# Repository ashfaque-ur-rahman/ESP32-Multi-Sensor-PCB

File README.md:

# ESP32-C3 Multi-Sensor PCB — 4-Layer Board
 
My most complex PCB design to date — an ESP32-C3 based multi-sensor IoT board featuring three sensors across a hierarchical, multi-sheet schematic. Designed over multiple days following the **Tech Explorations** tutorial series. This was my first experience with both 4-layer PCB stackup design and microphone amplifier circuit design.
 
---
 
## Preview
 
### Schematic — Root Page

### Schematic — Sensors Sheet

### Schematic — Page 2

### Schematic — User Interface Sheet

### PCB Layout

### 3D View

---
 
## Project overview
 
| Property | Details |
|---|---|
| **MCU** | ESP32-C3 |
| **Board layers** | 4-layer stackup |
| **Schematic structure** | Hierarchical — 3 separate sheets |
| **Sensors** | BME280, Electret Microphone + MAX4466EXK |
| **EDA Tool** | KiCad 9.0 |
| **Design reference** | Tech Explorations tutorial series |
| **Status** | Design complete |
 
---
 
## Board stackup
 
| Layer | Function |
|---|---|
| Layer 1 (Top) | Signal + components |
| Layer 2 | Ground plane (GND) |
| Layer 3 | Power plane (VCC) |
| Layer 4 (Bottom) | Signal |
 
A dedicated ground plane on Layer 2 ensures low-impedance returns for all sensors and clean power distribution — critical for analog microphone signal integrity.
 
---
 
## Sensors & key components
 
| Component | Part | Function | Interface |
|---|---|---|---|
| Environmental Sensor | BME280 (Bosch) | Temperature, humidity & pressure — 3-in-1 | I²C / SPI |
| Microphone | CMC-5042PF-AC (Same Sky) | 6mm omnidirectional electret condenser mic | Analog |
| Mic Amplifier | MAX4466EXK (Analog Devices) | Low-noise microphone amplifier, SC-70 package | Analog |
| MCU | ESP32-C3-02 | Wi-Fi + Bluetooth 5.0 LE microcontroller | — |
 
---
 
## Schematic structure
 
This design uses a **hierarchical multi-sheet schematic** — a professional approach for managing complex designs:
 
| Sheet | Contents |
|---|---|
| `Root page 1` | Top-level hierarchy, power distribution, ESP32-C3 core |
| `sensors.kicad_sch` | BME280 environmental sensor + microphone + MAX4466 amplifier circuit |
| `user_interface.kicad_sch` | User-facing connections, GPIO breakouts, connectors |
 
---
 
## Files included
 
### KiCad project files
| File | Description |
|---|---|
| `1st_ESP32_Demo_project.kicad_pro` | KiCad project file |
| `1st_ESP32_Demo_project.kicad_sch` | Root schematic |
| `ESP32-C3-02.kicad_sch` | ESP32-C3 sub-schematic sheet |
| `sensors.kicad_sch` | Sensors sub-schematic sheet |
| `user_interface.kicad_sch` | User interface sub-schematic sheet |
| `1st_ESP32_Demo_project.kicad_pcb` | PCB layout |
| `Footprints/` | Custom footprint library |
 
---
 
## What I learned
 
- 4-layer PCB stackup design with dedicated ground and power planes
- Hierarchical multi-sheet schematic design in KiCad 9.0
- BME280 I²C sensor integration with proper decoupling
- Electret condenser microphone biasing and signal conditioning
- MAX4466EXK low-noise amplifier circuit design
- Analog signal routing considerations on a mixed-signal PCB
- ESP32-C3 peripheral assignment and RF antenna clearance
---
 
## Tools used

---
 
## Reference
 
This design follows the **Tech Explorations ESP32 PCB Design tutorial series**.
 
> Tech Explorations: [https://www.youtube.com/@TechExplorations](https://www.youtube.com/@TechExplorations)
 
---
 
*Mymensingh Engineering College — EEE Department*

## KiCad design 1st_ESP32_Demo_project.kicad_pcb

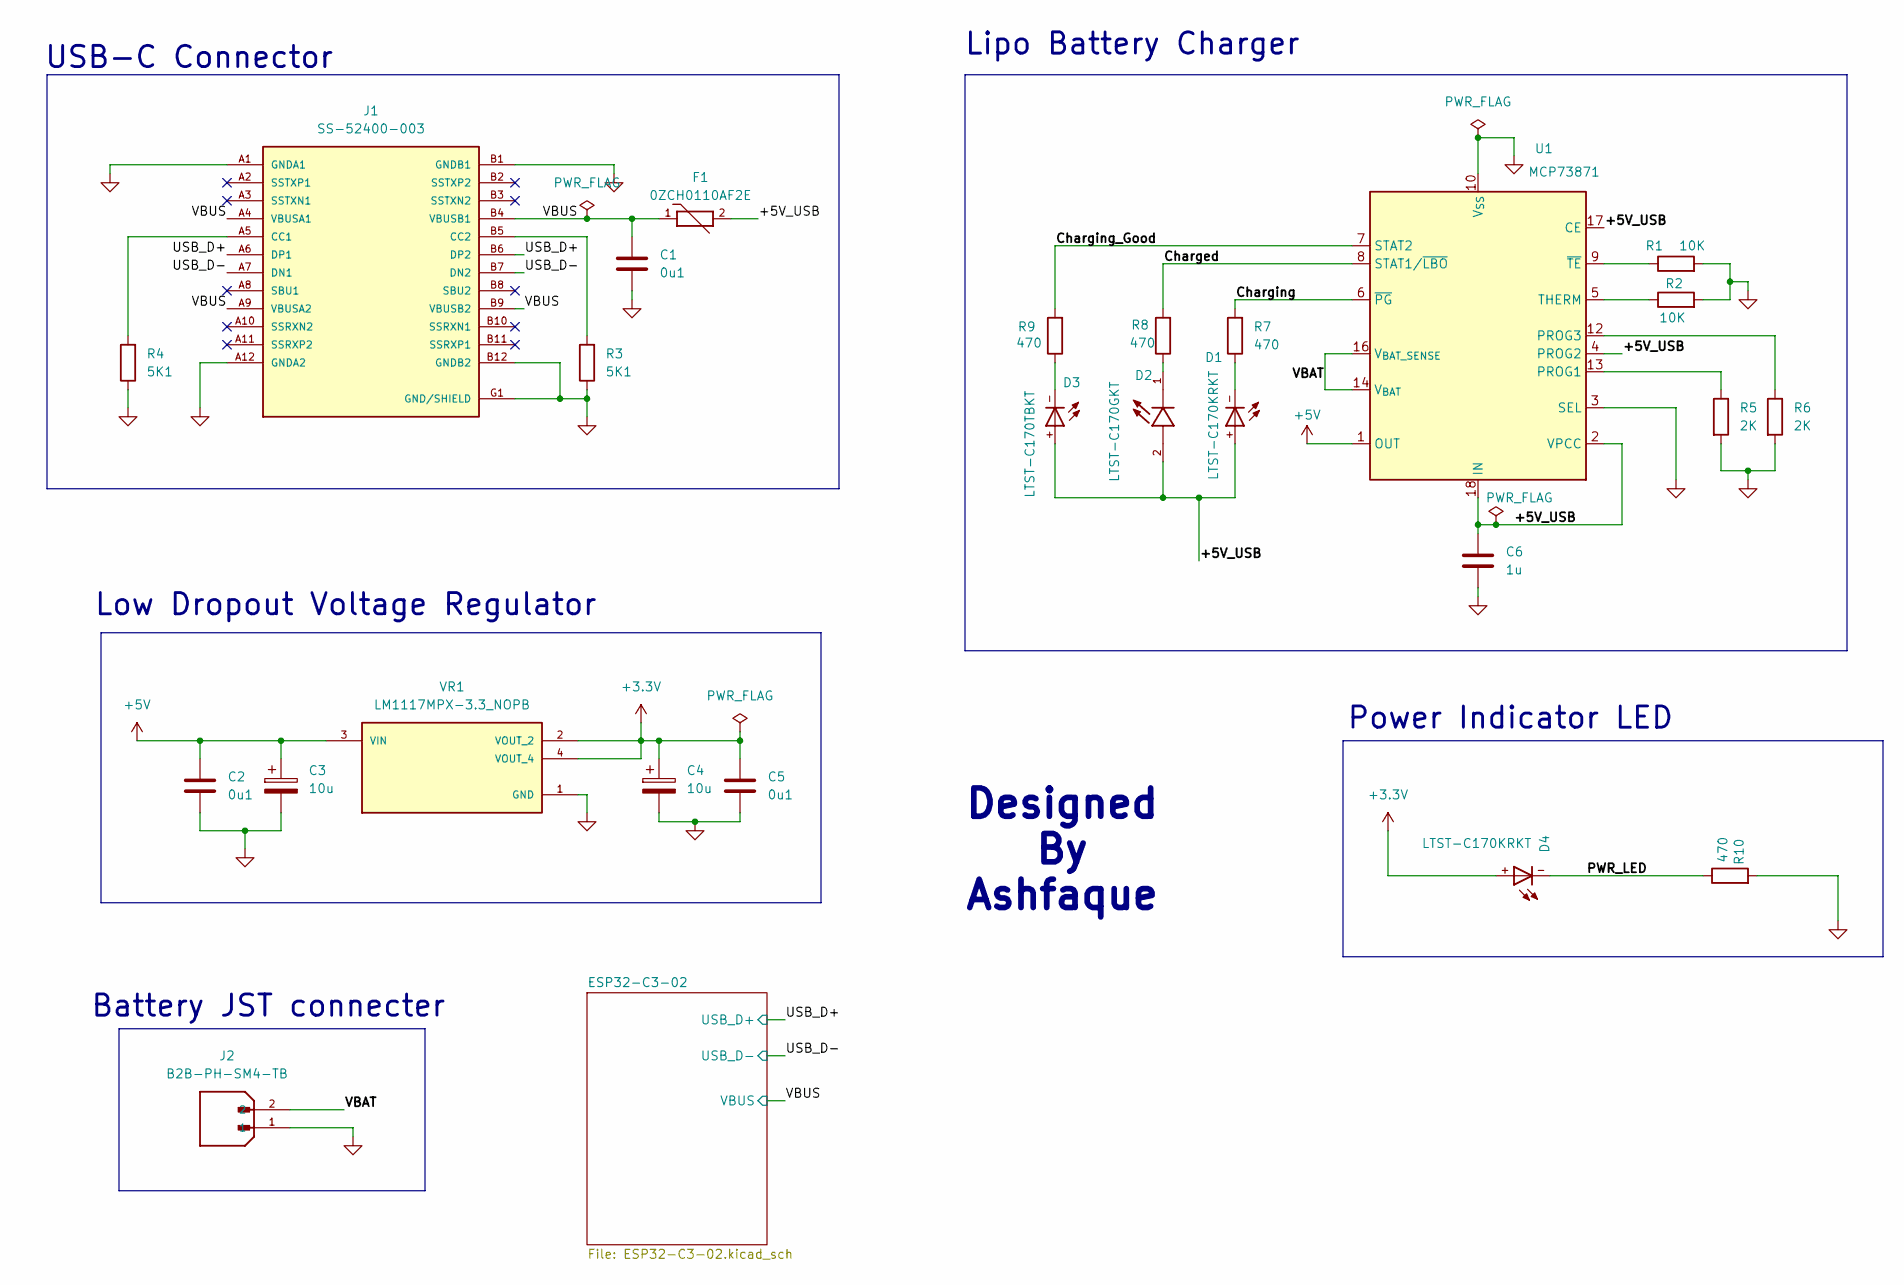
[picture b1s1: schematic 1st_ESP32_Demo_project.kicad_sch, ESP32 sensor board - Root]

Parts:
C1, C2, C5: 0u1; C_0805_2012Metric
C3, C4: 10u; CP_EIA-2012-12_Kemet-R
C6: 1u; C_0805_2012Metric
D1, D4: LTST-C170KRKT; DIOC200X125X110
D2: LTST-C170GKT; LED_LTST-C170GKT; PARTREV I
D3: LTST-C170TBKT; DIOC200X125X110
F1: 0ZCH0110AF2E; FUSC3225X100N; PARTREV Apr2023
J1: SS-52400-003; BELFUSE_SS-52400-003; PARTREV A0
J2: B2B-PH-SM4-TB; JST_B2B-PH-SM4-TB; PARTREV N/A
R1, R2: 10K; R_0805_2012Metric
R3, R4: 5K1; R_0805_2012Metric
R5, R6: 2K; R_0805_2012Metric
R7, R8, R9, R10: 470; R_0805_2012Metric
U1: MCP73871; QFN-20-1EP_4x4mm_P0.5mm_EP2.5x2.5mm
VR1: LM1117MPX-3.3_NOPB; VREG_LM1117MPX-3.3_NOPB; PARTREV O

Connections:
+3.3V: C4.1, C5.1, D4.+, VR1.2 (VOUT_2), VR1.4 (VOUT_4); also elsewhere on the board
+5V: C2.1, C3.1, U1.1 (OUT), U1.20 (OUT), VR1.3 (VIN)
/+5V_USB: C6.1, D1.+, D2.2, D3.+, F1.2, U1.2 (VPCC), U1.4 (PROG2), U1.17 (CE), U1.18 (IN), U1.19 (IN); also elsewhere on the board
/Charged: R8.2, U1.8 (STAT1/~LBO)
/Charging: R7.2, U1.6 (~PG)
/Charging_Good: R9.2, U1.7 (STAT2)
/PWR_LED: D4.-, R10.1
/USB_D+: J1.A6 (DP1), J1.B6 (DP2); also elsewhere on the board
/USB_D-: J1.A7 (DN1), J1.B7 (DN2); also elsewhere on the board
/VBAT: J2.2, U1.14 (V_{BAT}), U1.15 (V_{BAT}), U1.16 (V_{BAT_SENSE})
/VBUS: C1.1, F1.1, J1.A4 (VBUSA1), J1.A9 (VBUSA2), J1.B4 (VBUSB1), J1.B9 (VBUSB2); also elsewhere on the board
GND: C1.2, C2.2, C3.2, C4.2, C5.2, C6.2, J1.A1 (GNDA1), J1.A12 (GNDA2), J1.B1 (GNDB1), J1.B12 (GNDB2), J1.G1 (GND/SHIELD), J1.G2 (GND/SHIELD), J1.G3 (GND/SHIELD), J1.G4 (GND/SHIELD), J1.S1 (GND/SHIELD), J1.S2 (GND/SHIELD), J1.S3 (GND/SHIELD), J1.S4 (GND/SHIELD), J2.1, R1.2, R2.2, R3.1, R4.1, R5.2, R6.2, R10.2, U1.3 (SEL), U1.10 (V_{SS}), U1.11 (V_{SS}), U1.21 (V_{SS}), VR1.1 (GND); also elsewhere on the board
unnamed 35: D1.-, R7.1; also elsewhere on the board
unnamed 36: D2.1, R8.1; also elsewhere on the board
unnamed: D3.-, R9.1
unnamed: J1.A5 (CC1), R4.2
unnamed: J1.B5 (CC2), R3.2
unnamed: R5.1, U1.13 (PROG1)
unnamed: R6.1, U1.12 (PROG3)
unnamed: R2.1, U1.5 (THERM)
unnamed: R1.1, U1.9 (~TE)

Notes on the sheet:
Lipo Battery Charger
USB-C Connector
Battery JST connecter
Designed By Ashfaque
Power Indicator LED
Low Dropout Voltage Regulator

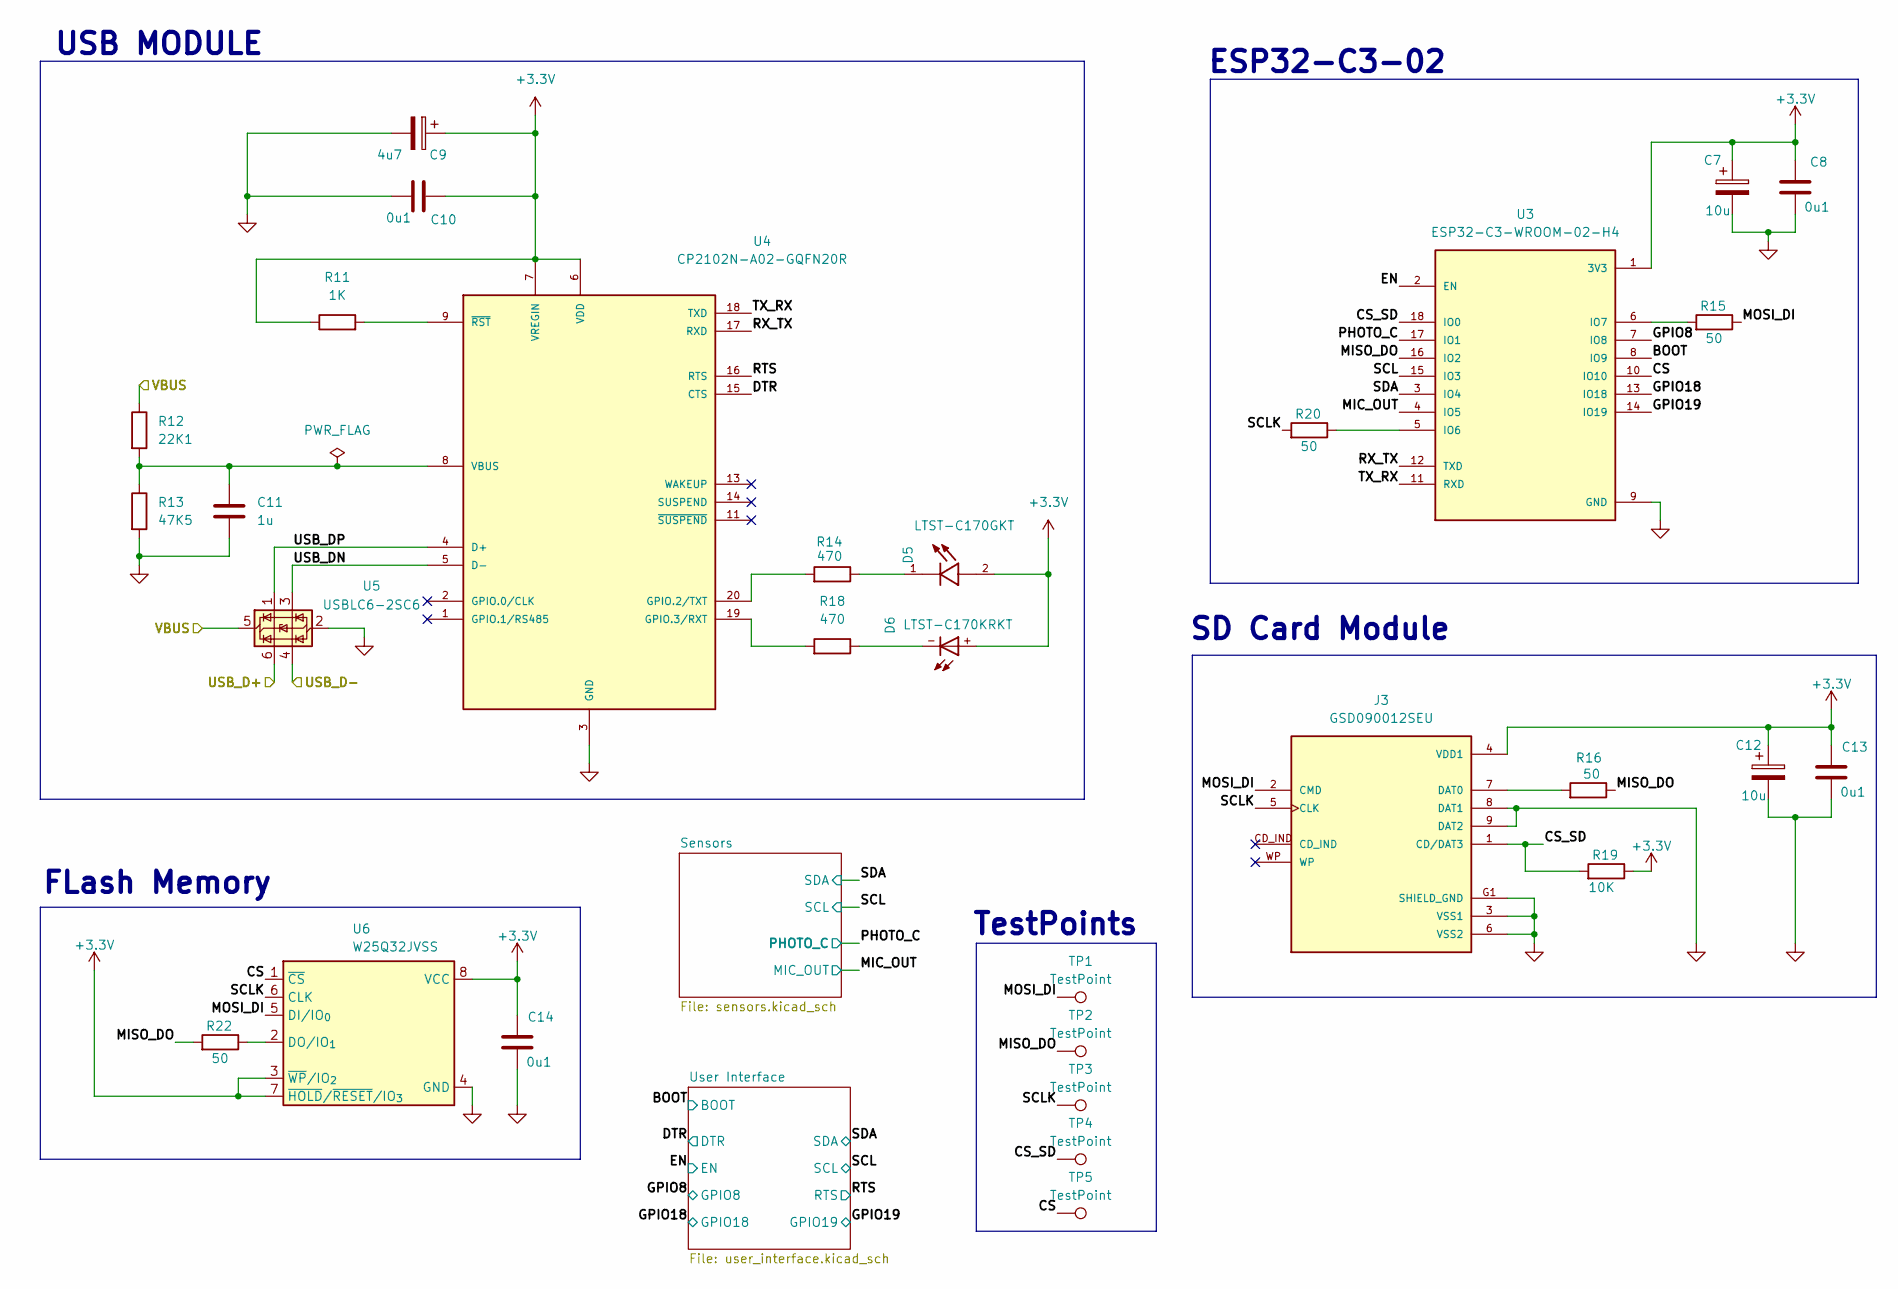
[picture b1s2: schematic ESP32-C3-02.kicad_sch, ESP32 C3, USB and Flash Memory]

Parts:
C7, C12: 10u; CP_EIA-2012-12_Kemet-R
C8, C10, C13, C14: 0u1; C_0805_2012Metric
C9: 4u7; CP_EIA-2012-12_Kemet-R
C11: 1u; C_0805_2012Metric
D5: LTST-C170GKT; LED_LTST-C170GKT; PARTREV I
D6: LTST-C170KRKT; DIOC200X125X110
J3: GSD090012SEU; AMPHENOL_GSD090012SEU; PARTREV E
R11: 1K; R_0805_2012Metric
R12: 22K1; R_0805_2012Metric
R13: 47K5; R_0805_2012Metric
R14, R18: 470; R_0805_2012Metric
R15, R16, R20, R22: 50; R_0805_2012Metric
R19: 10K; R_0805_2012Metric
TP1, TP2, TP3, TP4, TP5: TestPoint; TestPoint_Pad_D1.0mm
U3: ESP32-C3-WROOM-02-H4; MODULE_ESP32-C3-WROOM-02-H4
U4: CP2102N-A02-GQFN20R; SiliconLabs_QFN-20-1EP_3x3mm_P0.5mm_EP1.8x1.8mm; PARTREV 1.3
U5: USBLC6-2SC6; SOT-23-6
U6: W25Q32JVSS; SOIC-8_5.3x5.3mm_P1.27mm

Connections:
+3.3V: C7.1, C8.2, C9.1, C10.2, C12.1, C13.2, C14.2, D5.2, D6.+, J3.4 (VDD1), R11.1, R19.1, U3.1 (3V3), U4.6 (VDD), U4.7 (VREGIN), U6.3 (~WP/IO_{2}), U6.7 (~HOLD/~RESET/IO_{3}), U6.8 (VCC); also elsewhere on the board
/ESP32-C3-02/BOOT: U3.8 (IO9); also elsewhere on the board
/ESP32-C3-02/CS: TP5.1, U3.10 (IO10), U6.1 (~CS); also elsewhere on the board
/ESP32-C3-02/CS_SD: J3.1 (CD/DAT3), R19.2, TP4.1, U3.18 (IO0); also elsewhere on the board
/ESP32-C3-02/DTR: U4.15 (CTS); also elsewhere on the board
/ESP32-C3-02/EN: U3.2 (EN); also elsewhere on the board
/ESP32-C3-02/GPIO8: U3.7 (IO8); also elsewhere on the board
/ESP32-C3-02/GPIO18: U3.13 (IO18); also elsewhere on the board
/ESP32-C3-02/GPIO19: U3.14 (IO19); also elsewhere on the board
/ESP32-C3-02/MIC_OUT: U3.4 (IO5); also elsewhere on the board
/ESP32-C3-02/MISO_DO: R16.1, R22.2, TP2.1, U3.16 (IO2); also elsewhere on the board
/ESP32-C3-02/MOSI_DI: J3.2 (CMD), R15.1, TP1.1, U6.5 (DI/IO_{0}); also elsewhere on the board
/ESP32-C3-02/PHOTO_C: U3.17 (IO1); also elsewhere on the board
/ESP32-C3-02/RTS: U4.16 (RTS); also elsewhere on the board
/ESP32-C3-02/RX_TX: U3.12 (TXD), U4.17 (RXD)
/ESP32-C3-02/SCL: U3.15 (IO3); also elsewhere on the board
/ESP32-C3-02/SCLK: J3.5 (CLK), R20.2, TP3.1, U6.6 (CLK); also elsewhere on the board
/ESP32-C3-02/SDA: U3.3 (IO4); also elsewhere on the board
/ESP32-C3-02/TX_RX: U3.11 (RXD), U4.18 (TXD)
/ESP32-C3-02/USB_DN: U4.5 (D-), U5.3 (I/O2)
/ESP32-C3-02/USB_DP: U4.4 (D+), U5.1 (I/O1)
/USB_D+: U5.6 (I/O1); also elsewhere on the board
/USB_D-: U5.4 (I/O2); also elsewhere on the board
/VBUS: R12.1, U5.5 (VBUS); also elsewhere on the board
GND: C7.2, C8.1, C9.2, C10.1, C11.2, C12.2, C13.1, C14.1, J3.3 (VSS1), J3.6 (VSS2), J3.8 (DAT1), J3.9 (DAT2), J3.G1 (SHIELD_GND), J3.G2 (SHIELD_GND), J3.G3 (SHIELD_GND), J3.G4 (SHIELD_GND), R13.2, U3.9 (GND), U3.19 (GND), U3.20 (GND), U3.21 (GND), U3.22 (GND), U3.23 (GND), U3.24 (GND), U3.25 (GND), U3.26 (GND), U3.27 (GND), U3.28 (GND), U3.29 (GND), U3.30 (GND), U3.31 (GND), U3.32 (GND), U3.33 (GND), U3.34 (GND), U3.35 (GND), U3.36 (GND), U3.37 (GND), U3.38 (GND), U3.39 (GND), U4.3 (GND), U4.12 (GND), U4.21 (GND), U5.2 (GND), U6.4 (GND); also elsewhere on the board
unnamed: D5.1, R14.1
unnamed: D6.-, R18.1
unnamed: J3.7 (DAT0), R16.2
unnamed: R20.1, U3.5 (IO6)
unnamed: R15.2, U3.6 (IO7)
unnamed: R14.2, U4.20 (GPIO.2/TXT)
unnamed: R18.2, U4.19 (GPIO.3/RXT)
unnamed: C11.1, R12.2, R13.1, U4.8 (VBUS)
unnamed: R11.2, U4.9 (~RST)
unnamed: R22.1, U6.2 (DO/IO_{1})

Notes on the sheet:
USB MODULE
FLash Memory
ESP32-C3-02
TestPoints
SD Card Module

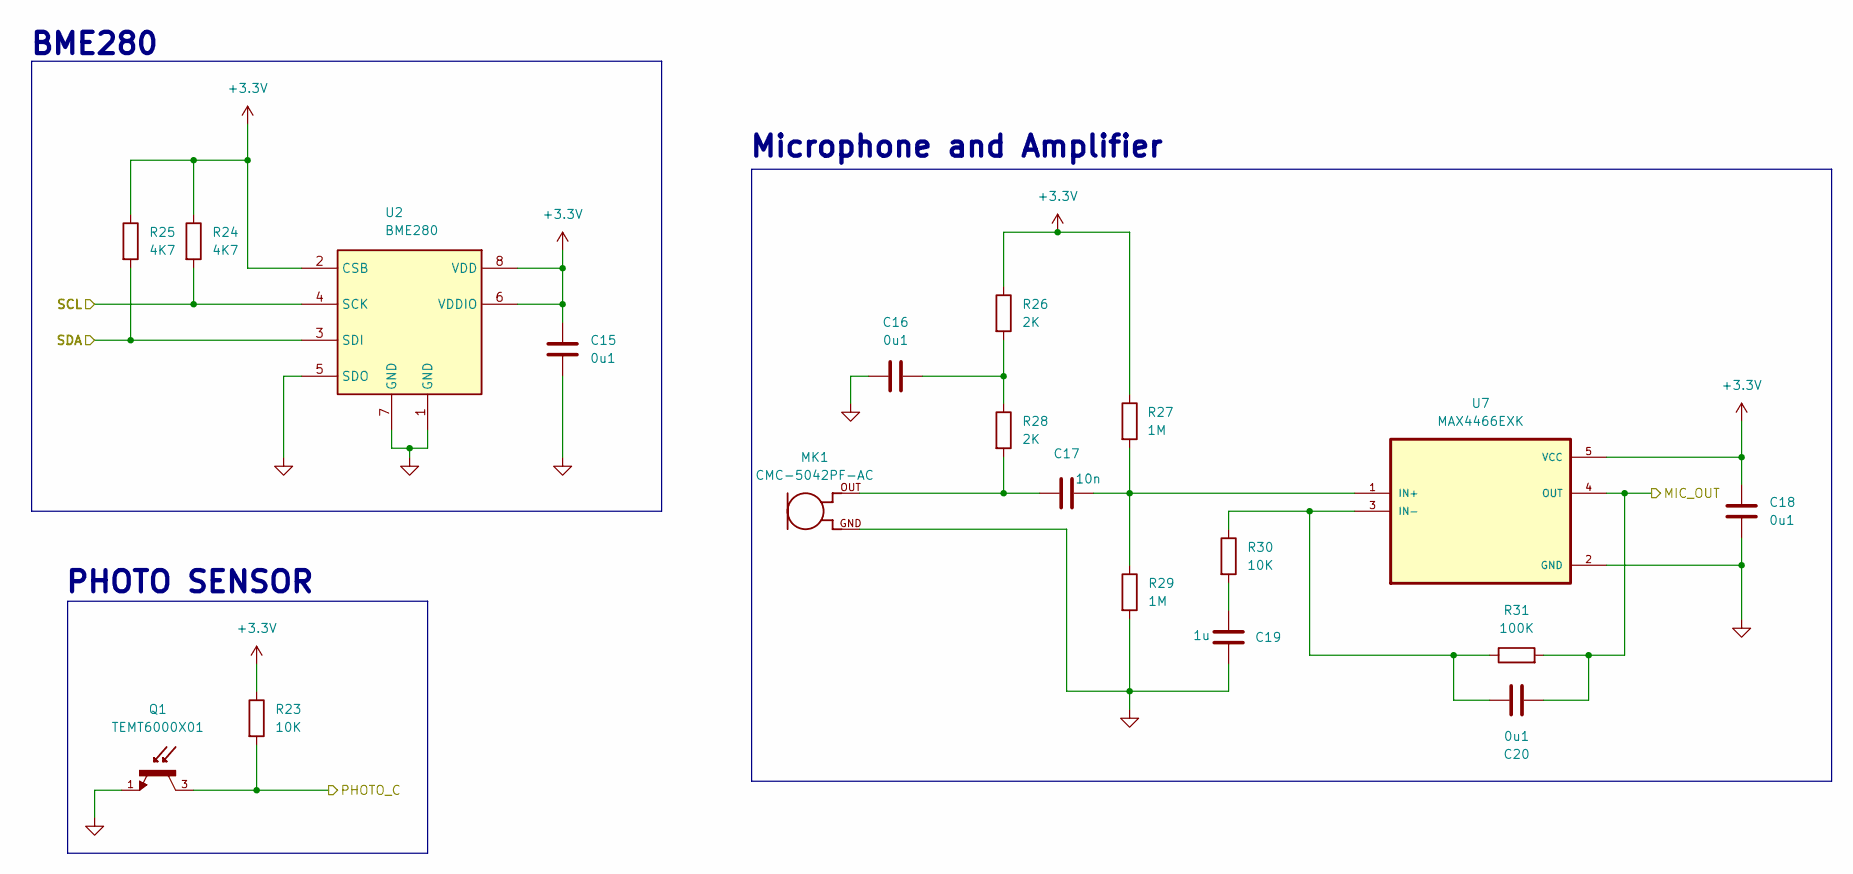
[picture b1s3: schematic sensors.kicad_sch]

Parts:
C15, C16, C18, C20: 0u1; C_0805_2012Metric
C17: 10n; C_0805_2012Metric
C19: 1u; C_0805_2012Metric
MK1: CMC-5042PF-AC; CUI_CMC-5042PF-AC
Q1: TEMT6000X01; TRANS_TEMT6000X01; PARTREV 1.9
R23, R30: 10K; R_0805_2012Metric
R24, R25: 4K7; R_0805_2012Metric
R26, R28: 2K; R_0805_2012Metric
R27, R29: 1M; R_0805_2012Metric
R31: 100K; R_0805_2012Metric
U2: BME280; Bosch_LGA-8_2.5x2.5mm_P0.65mm_ClockwisePinNumbering
U7: MAX4466EXK; SOT65P210X110-5N

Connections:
+3.3V: C15.1, C18.1, R23.1, R24.1, R25.1, R26.1, R27.1, U2.2 (CSB), U2.6 (VDDIO), U2.8 (VDD), U7.5 (VCC); also elsewhere on the board
/ESP32-C3-02/MIC_OUT: C20.2, R31.2, U7.4 (OUT); also elsewhere on the board
/ESP32-C3-02/PHOTO_C: Q1.3, R23.2; also elsewhere on the board
/ESP32-C3-02/SCL: R24.2, U2.4 (SCK); also elsewhere on the board
/ESP32-C3-02/SDA: R25.2, U2.3 (SDI); also elsewhere on the board
GND: C15.2, C16.1, C18.2, C19.1, MK1.GND, Q1.1, R29.2, U2.1 (GND), U2.5 (SDO), U2.7 (GND), U7.2 (GND); also elsewhere on the board
unnamed: C16.2, R26.2, R28.1
unnamed: C17.2, MK1.OUT, R28.2
unnamed: C19.2, R30.2
unnamed: C17.1, R27.2, R29.1, U7.1 (IN+)
unnamed: C20.1, R30.1, R31.1, U7.3 (IN-)

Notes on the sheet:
BME280
Microphone and Amplifier
PHOTO SENSOR

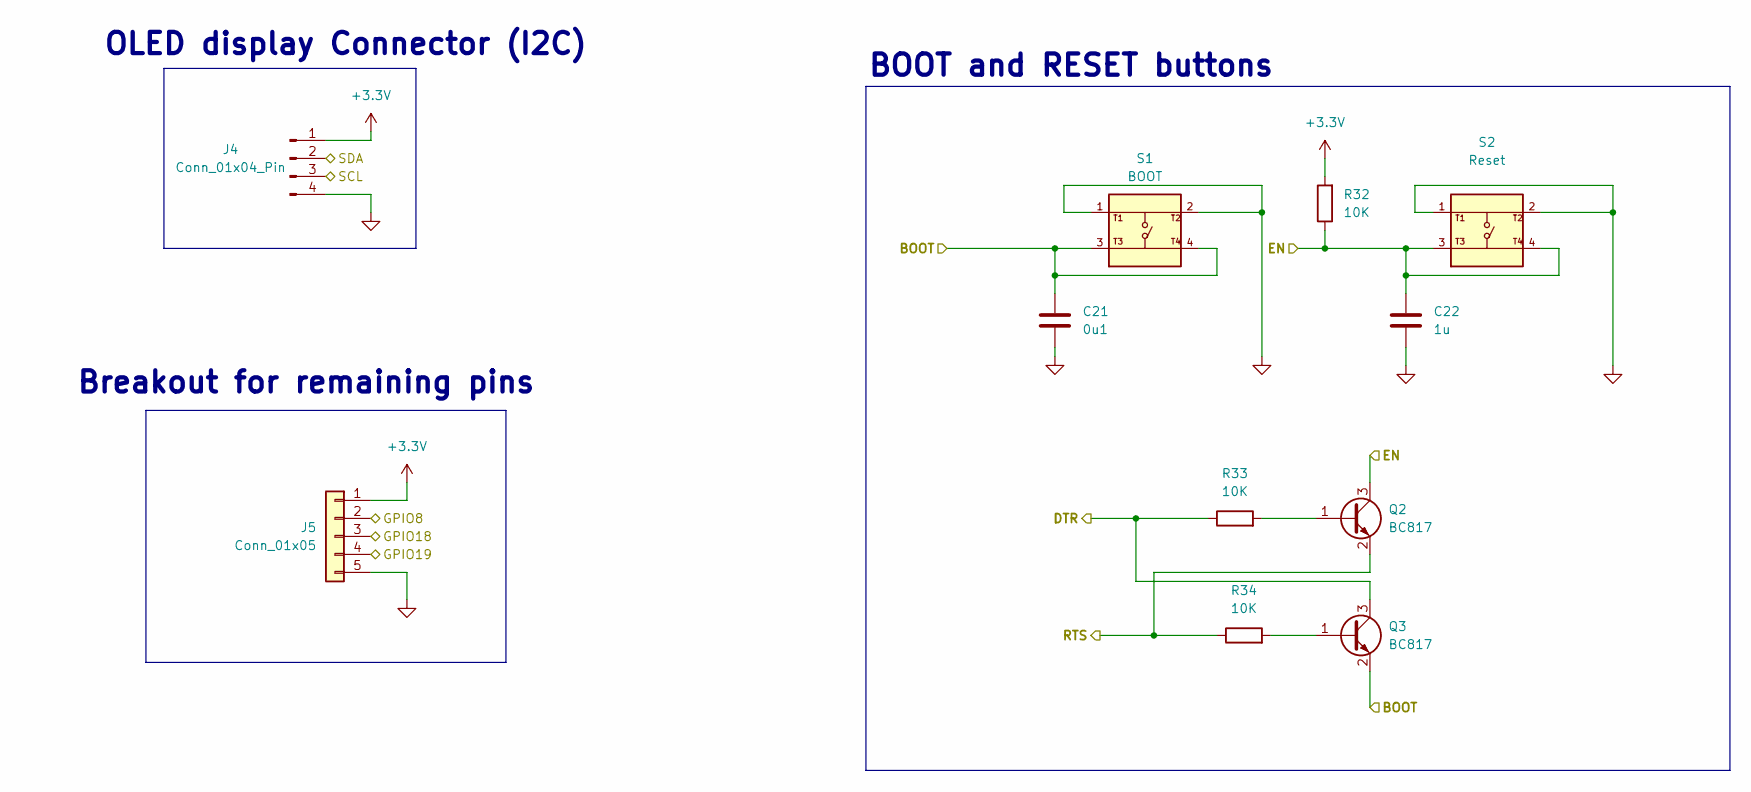
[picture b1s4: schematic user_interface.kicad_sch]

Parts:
C21: 0u1; C_0805_2012Metric
C22: 1u; C_0805_2012Metric
J4: Conn_01x04_Pin; PinHeader_1x04_P2.54mm_Vertical
J5: Conn_01x05; PinHeader_1x05_P2.54mm_Vertical
Q2, Q3: BC817; SOT-23
R32, R33, R34: 10K; R_0805_2012Metric
S1: BOOT; SW_USLPT2819DT2TR; PARTREV P
S2: Reset; SW_USLPT2819DT2TR; PARTREV P

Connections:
+3.3V: J4.1, J5.1, R32.2; also elsewhere on the board
/ESP32-C3-02/BOOT: C21.1, Q3.2 (E), S1.3, S1.4; also elsewhere on the board
/ESP32-C3-02/DTR: Q3.3 (C), R33.1; also elsewhere on the board
/ESP32-C3-02/EN: C22.1, Q2.3 (C), R32.1, S2.3, S2.4; also elsewhere on the board
/ESP32-C3-02/GPIO8: J5.2; also elsewhere on the board
/ESP32-C3-02/GPIO18: J5.3; also elsewhere on the board
/ESP32-C3-02/GPIO19: J5.4; also elsewhere on the board
/ESP32-C3-02/RTS: Q2.2 (E), R34.1; also elsewhere on the board
/ESP32-C3-02/SCL: J4.3; also elsewhere on the board
/ESP32-C3-02/SDA: J4.2; also elsewhere on the board
GND: C21.2, C22.2, J4.4, J5.5, S1.1, S1.2, S2.1, S2.2; also elsewhere on the board
unnamed: Q2.1 (B), R33.2
unnamed: Q3.1 (B), R34.2

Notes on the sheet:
OLED display Connector (I2C)
Breakout for remaining pins
BOOT and RESET buttons

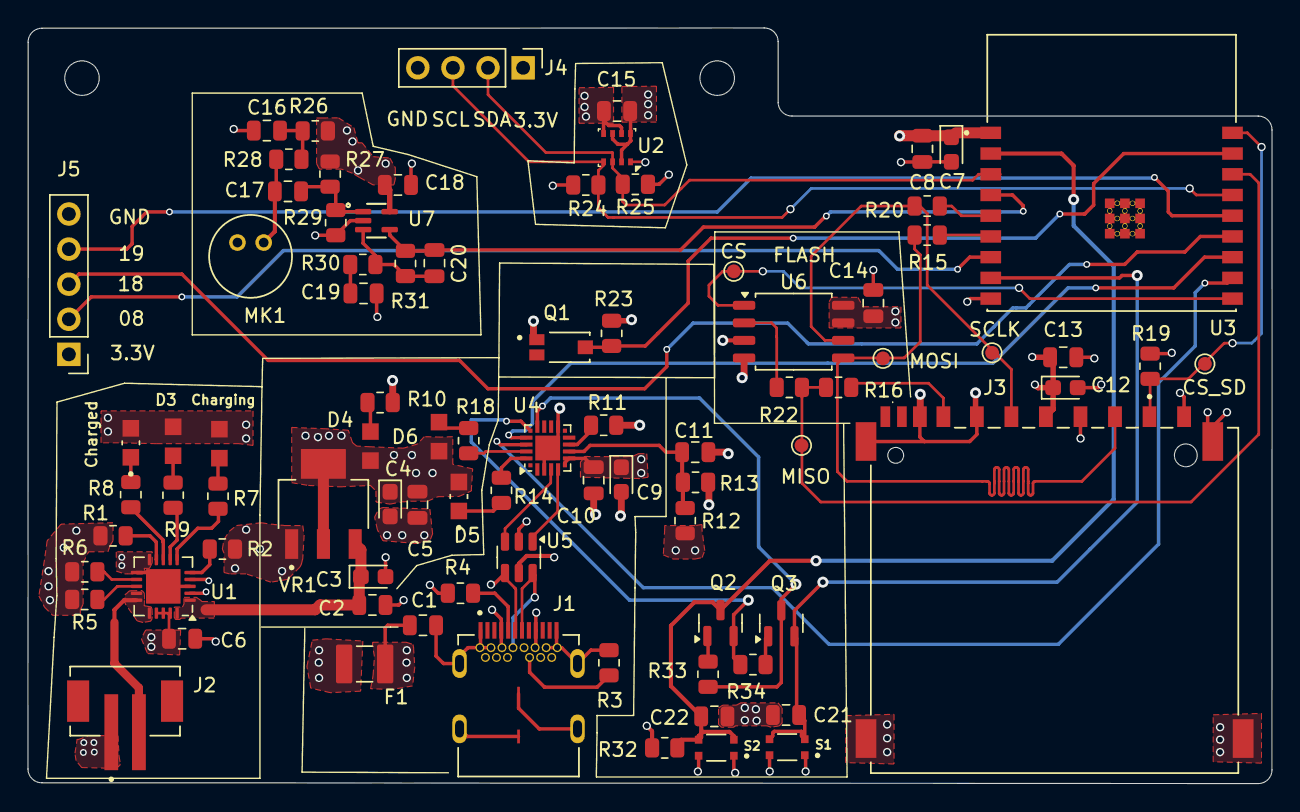
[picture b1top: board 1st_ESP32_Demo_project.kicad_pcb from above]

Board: 4 copper layers, 90.0 x 54.7 mm, 85 parts (0 on the bottom side), 58 nets.

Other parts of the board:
CS: TestPoint; TestPoint_Pad_D1.0mm
CS_SD: TestPoint; TestPoint_Pad_D1.0mm
Charged: LTST-C170GKT; LED_LTST-C170GKT
Charging: LTST-C170KRKT; DIOC200X125X110
MISO: TestPoint; TestPoint_Pad_D1.0mm
MOSI: TestPoint; TestPoint_Pad_D1.0mm
SCLK: TestPoint; TestPoint_Pad_D1.0mm

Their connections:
/+5V_USB: Charged.2, Charging.+; also elsewhere on the board
/ESP32-C3-02/CS: CS.1; also elsewhere on the board
/ESP32-C3-02/CS_SD: CS_SD.1; also elsewhere on the board
/ESP32-C3-02/MISO_DO: MISO.1; also elsewhere on the board
/ESP32-C3-02/MOSI_DI: MOSI.1; also elsewhere on the board
/ESP32-C3-02/SCLK: SCLK.1; also elsewhere on the board
unnamed 35: Charging.-; also elsewhere on the board
unnamed 36: Charged.1; also elsewhere on the board
